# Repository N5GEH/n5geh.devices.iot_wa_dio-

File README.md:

#   IoT-DIO <br/> Digital IO IoT Wireless Adapter

IoT-DIO is a wireless adapter for developing IoT applications for Industrial and Building Automation Systems based on the Espressif chipset ESP32. The adapter is compatible with:
- RS485
- M-Bus
- Ethernet

The library allows the implemention of IoT applications that rely on MQTT protocol via WiFi/NB-IoT/LTE Cat-M1 interfaces.

## Adapter versions
The Iot-DIO wireless adapter is available in two versions developed using [KiCAD 5.1](https://kicad.org/) and compatible with:
- [ESP32-PICO-KIT v4](https://docs.espressif.com/projects/esp-idf/en/latest/esp32/hw-reference/esp32/get-started-pico-kit.html) - is an ESP32-based mini development board produced by [Espressif](https://espressif.com/). The board features integrated Wifi and BLE capabilites.
- [FiPy](https://pycom.io/product/fipy/) - is an ESP32-based mini development board produced by [Pycom](https://pycom.io/). The board features integrated Wifi, BLE, LoRa, Sigfox, NB-IoT and LTE Cat-M1 capabilities.

## Development Framework
IoT-DIO relies on the Espressif IoT Development Framework [ESP-IDF](https://github.com/espressif/esp-idf), the official development framework for the [ESP32](https://espressif.com/en/products/hardware/esp32/overview) chip.

## Configuration

### Pinout
IO pinout (top-down):
- 0: V_BUS
- 1: M-/B-
- 2: M+/A+
- 3: GND

### Functions button
The push button BT performs multiple operations depending on the pressure time Tp.

| Pressure Time   |      Action                                                                      |
|:---------------:|:---------------------------------------------------------------------------------|
|     Tp < 1s     | Performs a soft-reset of the adapter                                             |
|1s < Tp < 5s     | Enables the AP mode. If not previously changed, the device will be visible by default with the SSID `ESP_<MAC>`, where <MAC> is the MAC address of the adapter network interface in hex format|
|5s < Tp          | Performs a hard-reset of the adapter deleting the previously stored configuration|

# Publications

We kindly ask academic publications employing based or inspired to IoT-AIO to cite at least one of the following papers:

- M.H. Schraven, C. Guarnieri Calò Carducci, M.A. Baranski, D. Mueller, A. Monti, “Designing a Development Board for Research on IoT Appli-cations in Building Automation Systems,” 36th International Symposiumon  Automation  and  Robotics  in  Construction  (ISARC  2019),  Banff,Canada, 2019, pp. 82-90, [DOI: 10.22260/ISARC2019/0012](https://doi.org/10.22260/ISARC2019/0012)
- C. Guarnieri Calò Carducci, A. Monti, M. H. Schraven, M. Schumacher and D. Mueller, “Enabling ESP32-based IoT Applications in Building Automation Systems,” 2019 II Workshop on Metrology for Industry 4.0 and IoT (MetroInd4.0&IoT), Naples, Italy, 2019, pp. 306-311, [DOI: 10.1109/METROI4.2019.8792852](https://doi.org/10.1109/METROI4.2019.8792852)

# Copyright

2019-2020, Institute for Automation of Complex Power Systems, EONERC  

# License

<br />This work is licensed under a <a rel="license" href="http://creativecommons.org/licenses/by/4.0/">Creative Commons Attribution 4.0 International License</a>.

# Contact

- [Carlo Guarnieri Calò Carducci (PhD)](mailto:cguarnieri@eonerc.rwth-aachen.de)

[Institute for Automation of Complex Power Systems (ACS)](http://www.acs.eonerc.rwth-aachen.de)  
[EON Energy Research Center (EONERC)](http://www.eonerc.rwth-aachen.de)  
[RWTH University Aachen, Germany](http://www.rwth-aachen.de)

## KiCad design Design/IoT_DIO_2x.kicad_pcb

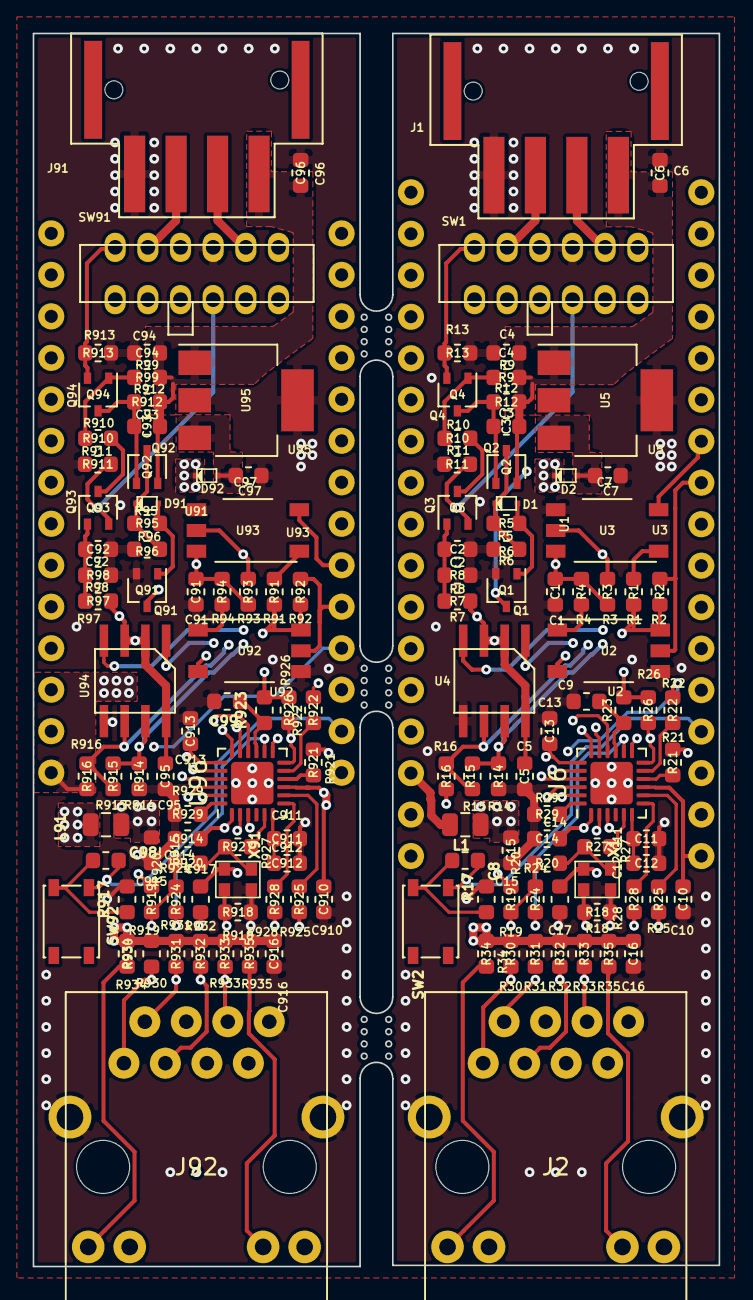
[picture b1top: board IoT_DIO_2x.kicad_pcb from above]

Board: 4 copper layers, 42.0 x 75.5 mm, 140 parts (0 on the bottom side), 109 nets.

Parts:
C1, C3, C5, C7, C8, C9, C10, C13, C14, C17, C91, C93, C95, C97, C98, C99, C910, C913, C914, C917: 100n; C_0603_1608Metric
C2, C12, C92, C912: 1u; C_0603_1608Metric
C4, C94: 10u; C_0603_1608Metric
C6, C96: 220n; C_0603_1608Metric
C11, C911: 470p; C_0603_1608Metric
C15, C915: 4.7u; C_0603_1608Metric
C16, C916: 22n; C_0603_1608Metric
D1, D2, D91, D92: D_Schottky BAS52-02V; BAS52
J1, J91: Conn_01x04 XW4L-04A1-H1; XW4L-04A1-H1
J2, J92: RJ45_LED_Shielded; HR911105A
L1, L91: BK2125HS470-T; L_0805_2012Metric
Q1, Q3, Q4, Q91, Q93, Q94: BC817-40WT1G; SOT-323_SC-70
Q2, Q92: BC857BWT1G; SOT-323_SC-70
R1, R34, R35, R91, R934, R935: 330; R_0603_1608Metric
R2, R7, R8, R11, R26, R92, R97, R98, R911, R926: 2.2k; R_0603_1608Metric
R3, R93: 3.3k; R_0603_1608Metric
R4, R94: 620; R_0603_1608Metric
R5, R13, R95, R913: 220k; R_0603_1608Metric
R6, R96: 22k; R_0603_1608Metric
R9, R10, R17, R18, R99, R910, R917, R918: 10k; R_0603_1608Metric
R12, R912: 82; R_0603_1608Metric
R14, R16, R914, R916: 220; R_0603_1608Metric
R15, R915: 120; R_0603_1608Metric
R19, R23, R919, R923: 4.7k; R_0603_1608Metric
R20, R24, R27, R30, R31, R32, R33, R920, R924, R927, R930, R931, R932, R933: 49.9; R_0603_1608Metric
R21, R22, R25, R28, R921, R922, R925, R928: 10; R_0603_1608Metric
R29, R929: 12.1k; R_0603_1608Metric
SW1, SW91: MS42R
SW2, SW92: PTS810SJK250SMTRLFS; SW_SPST_PTS810
U1: ESP-32-PICO-KIT-V4; ESP32v4
U2, U3, U92, U93: VOM452T; MFSOP6-5_4.4x3.6mm_P1.27mm
U4, U94: MAX13487EESA+; MAX13487
U5, U95: LM340MP-5.0/NOPB; SOT-223-3_TabPin2
U6, U96: LAN8720A-CP; QFN-24-1EP_4x4mm_P0.5mm_EP2.6x2.6mm
U91: FiPy
X1, X91: DSC6011JI1A-050.0000; Oscillator_DSC60xx_Microchip-4Pin_2.5x2.0mm

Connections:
+3V3: C10.1, C17.1, C910.1, C917.1, L1.1, L91.1, R1.2, R2.1, R19.2, R21.2, R23.2, R26.2, R91.2, R92.1, R919.2, R921.2, R923.2, R926.2, U1.1, U1.32, U2.6, U6.9, U91.26, U92.6, U96.9, X1.4, X91.4
+5V: C1.1, C5.1, C91.1, C95.1, D2.1, D92.1, R3.2, R4.1, R7.1, R16.1, R93.2, R94.1, R97.1, R916.1, U1.34, U3.6, U4.2, U4.3, U4.8, U91.28, U93.6, U94.2, U94.3, U94.8
/IoT_DIO_ESP/Ethernet/CRS_DV: R22.2, U1.24
/IoT_DIO_ESP/Ethernet/LED1: J2.10, U6.3
/IoT_DIO_ESP/Ethernet/LED2: J2.12, U6.2
/IoT_DIO_ESP/Ethernet/MDC: U1.14, U6.13
/IoT_DIO_ESP/Ethernet/MDIO: R26.1, U1.13, U6.12
/IoT_DIO_ESP/Ethernet/PHY_POWER: R18.2, U1.26, X1.1
/IoT_DIO_ESP/Ethernet/RXD0: R25.2, U1.20
/IoT_DIO_ESP/Ethernet/RXD1: R28.2, U1.21
/IoT_DIO_ESP/Ethernet/R_RXCLK: R19.1, R20.2, R24.2, U1.31
/IoT_DIO_ESP/Ethernet/TXD0: U1.15, U6.17
/IoT_DIO_ESP/Ethernet/TXD1: U1.16, U6.18
/IoT_DIO_ESP/Ethernet/TX_EN: U1.17, U6.16
/IoT_DIO_ESP/Ethernet/nRST: C9.1, R23.1, U6.15
/IoT_DIO_ESP/MBUS/M+: Q4.2, R13.1, SW1.7
/IoT_DIO_ESP/RS485/A+: R15.1, R16.2, SW1.9, U4.6
/IoT_DIO_ESP/RS485/B-: R14.1, R15.2, SW1.12, U4.7
/IoT_DIO_ESP/Rx_Mbus: Q1.3, SW1.1
/IoT_DIO_ESP/Rx_RS485: SW1.3, U4.1
/IoT_DIO_ESP/Tx_Mbus: Q3.2, R11.1, SW1.4
/IoT_DIO_ESP/Tx_RS485: SW1.6, U4.4
/IoT_DIO_FyPy/Ethernet1/CRS_DV: R922.2, U91.8
/IoT_DIO_FyPy/Ethernet1/LED1: J92.10, U96.3
/IoT_DIO_FyPy/Ethernet1/LED2: J92.12, U96.2
/IoT_DIO_FyPy/Ethernet1/MDC: U91.20, U96.13
/IoT_DIO_FyPy/Ethernet1/MDIO: R926.1, U91.19, U96.12
/IoT_DIO_FyPy/Ethernet1/PHY_POWER: R918.2, U91.25, X91.1
/IoT_DIO_FyPy/Ethernet1/RXD0: R925.2, U91.24
/IoT_DIO_FyPy/Ethernet1/RXD1: R928.2, U91.23
/IoT_DIO_FyPy/Ethernet1/R_RXCLK: R919.1, R920.2, R924.2, U91.4
/IoT_DIO_FyPy/Ethernet1/TXD0: U91.9, U96.17
/IoT_DIO_FyPy/Ethernet1/TXD1: U91.13, U96.18
/IoT_DIO_FyPy/Ethernet1/TX_EN: U91.14, U96.16
/IoT_DIO_FyPy/Ethernet1/nRST: C99.1, R923.1, U96.15
/IoT_DIO_FyPy/MBUS/M+: Q94.2, R913.1, SW91.7
/IoT_DIO_FyPy/RS485/A+: R915.1, R916.2, SW91.9, U94.6
/IoT_DIO_FyPy/RS485/B-: R914.1, R915.2, SW91.12, U94.7
/IoT_DIO_FyPy/Rx_Mbus: Q91.3, SW91.1
/IoT_DIO_FyPy/Rx_RS485: SW91.3, U94.1
/IoT_DIO_FyPy/Tx_Mbus: Q93.2, R911.1, SW91.4
/IoT_DIO_FyPy/Tx_RS485: SW91.6, U94.4
GND: C1.2, C2.2, C4.2, C5.2, C6.2, C7.2, C9.2, C10.2, C11.2, C12.2, C13.2, C14.2, C15.2, C16.2, C17.2, C91.2, C92.2, C94.2, C95.2, C96.2, C97.2, C99.2, C910.2, C911.2, C912.2, C913.2, C914.2, C915.2, C916.2, C917.2, J1.4, J2.8, J2.13, J2.14, J91.4, J92.8, J92.13, J92.14, Q1.2, Q91.2, R6.2, R8.2, R11.2, R13.2, R14.2, R17.2, R18.1, R29.1, R96.2, R98.2, R911.2, R913.2, R914.2, R917.2, R918.1, R929.1, SW1.10, SW91.10, U1.2, U1.33, U2.4, U3.4, U4.5, U5.2, U6.25, U91.27, U92.4, U93.4, U94.5, U95.2, U96.25, X1.2, X91.2
unnamed: C2.1, Q3.1, R7.2, R8.1
unnamed: C3.2, Q2.1, Q4.3, R12.2
unnamed: C7.1, D2.2, U5.3
unnamed: C8.1, SW2.4, U1.4
unnamed: C8.2, R17.1, SW2.2
unnamed: C11.1, C12.1, U6.6
unnamed: C92.1, Q93.1, R97.2, R98.1
unnamed: C93.2, Q92.1, Q94.3, R912.2
unnamed: C97.1, D92.2, U95.3
unnamed: C98.1, SW92.4, U91.2
unnamed: C98.2, R917.1, SW92.2
unnamed: C911.1, C912.1, U96.6
unnamed: D1.1, Q2.3, R5.1, R6.1
unnamed: D1.2, Q1.1, R5.2
unnamed: D91.1, Q92.3, R95.1, R96.1
unnamed: D91.2, Q91.1, R95.2
unnamed: J1.2, SW1.11
unnamed: J1.3, SW1.8
unnamed: J2.1, R30.1, U6.21
unnamed: J2.2, R31.1, U6.20
unnamed: J2.3, R32.1, U6.23
unnamed: J2.6, R33.1, U6.22
unnamed: J2.9, R34.1
unnamed: J2.11, R35.1
unnamed: J91.2, SW91.11
unnamed: J91.3, SW91.8
unnamed: J92.1, R930.1, U96.21
unnamed: J92.2, R931.1, U96.20
unnamed: J92.3, R932.1, U96.23
unnamed: J92.6, R933.1, U96.22
unnamed: J92.9, R934.1
unnamed: J92.11, R935.1
unnamed: Q3.3, R10.2
unnamed: Q4.1, R9.2, R10.1
unnamed: Q93.3, R910.2
unnamed: Q94.1, R99.2, R910.1
unnamed: R1.1, U3.1
unnamed: R2.2, U1.10, U2.5
unnamed: R3.1, SW1.5, U3.5
unnamed: R4.2, U2.1
unnamed: R20.1, R27.2, X1.3
unnamed: R21.1, U6.10
unnamed: R22.1, U6.11
unnamed: R24.1, U6.14
unnamed: R25.1, U6.8
unnamed: R27.1, U6.5
unnamed: R28.1, U6.7
unnamed: R29.2, U6.24
unnamed: R91.1, U93.1
unnamed: R92.2, U91.5, U92.5
unnamed: R93.1, SW91.5, U93.5
unnamed: R94.2, U92.1
unnamed: R920.1, R927.2, X91.3
unnamed: R921.1, U96.10
unnamed: R922.1, U96.11
unnamed: R924.1, U96.14
unnamed: R925.1, U96.8
unnamed: R927.1, U96.5
unnamed: R928.1, U96.7
unnamed: R929.2, U96.24
unnamed: SW1.2, U2.3
unnamed: SW91.2, U92.3
unnamed: U1.11, U3.3
unnamed: U91.6, U93.3
VBUS: C3.1, C4.1, C6.1, C93.1, C94.1, C96.1, J1.1, J91.1, Q2.2, Q92.2, R9.1, R12.1, R99.1, R912.1, U5.1, U95.1
VDDA: C13.1, C14.1, C15.1, C16.1, C913.1, C914.1, C915.1, C916.1, J2.4, J2.5, J92.4, J92.5, L1.2, L91.2, R30.2, R31.2, R32.2, R33.2, R34.2, R35.2, R930.2, R931.2, R932.2, R933.2, R934.2, R935.2, U6.1, U6.19, U96.1, U96.19

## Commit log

2020-06-27 Project migration
2020-07-09 Add LICENSE
2021-11-10 Update README.md
    https://forum.kicad.info/t/warning-avoid-all-links-to-kicad-pcb-org-use-kicad-org/31521
